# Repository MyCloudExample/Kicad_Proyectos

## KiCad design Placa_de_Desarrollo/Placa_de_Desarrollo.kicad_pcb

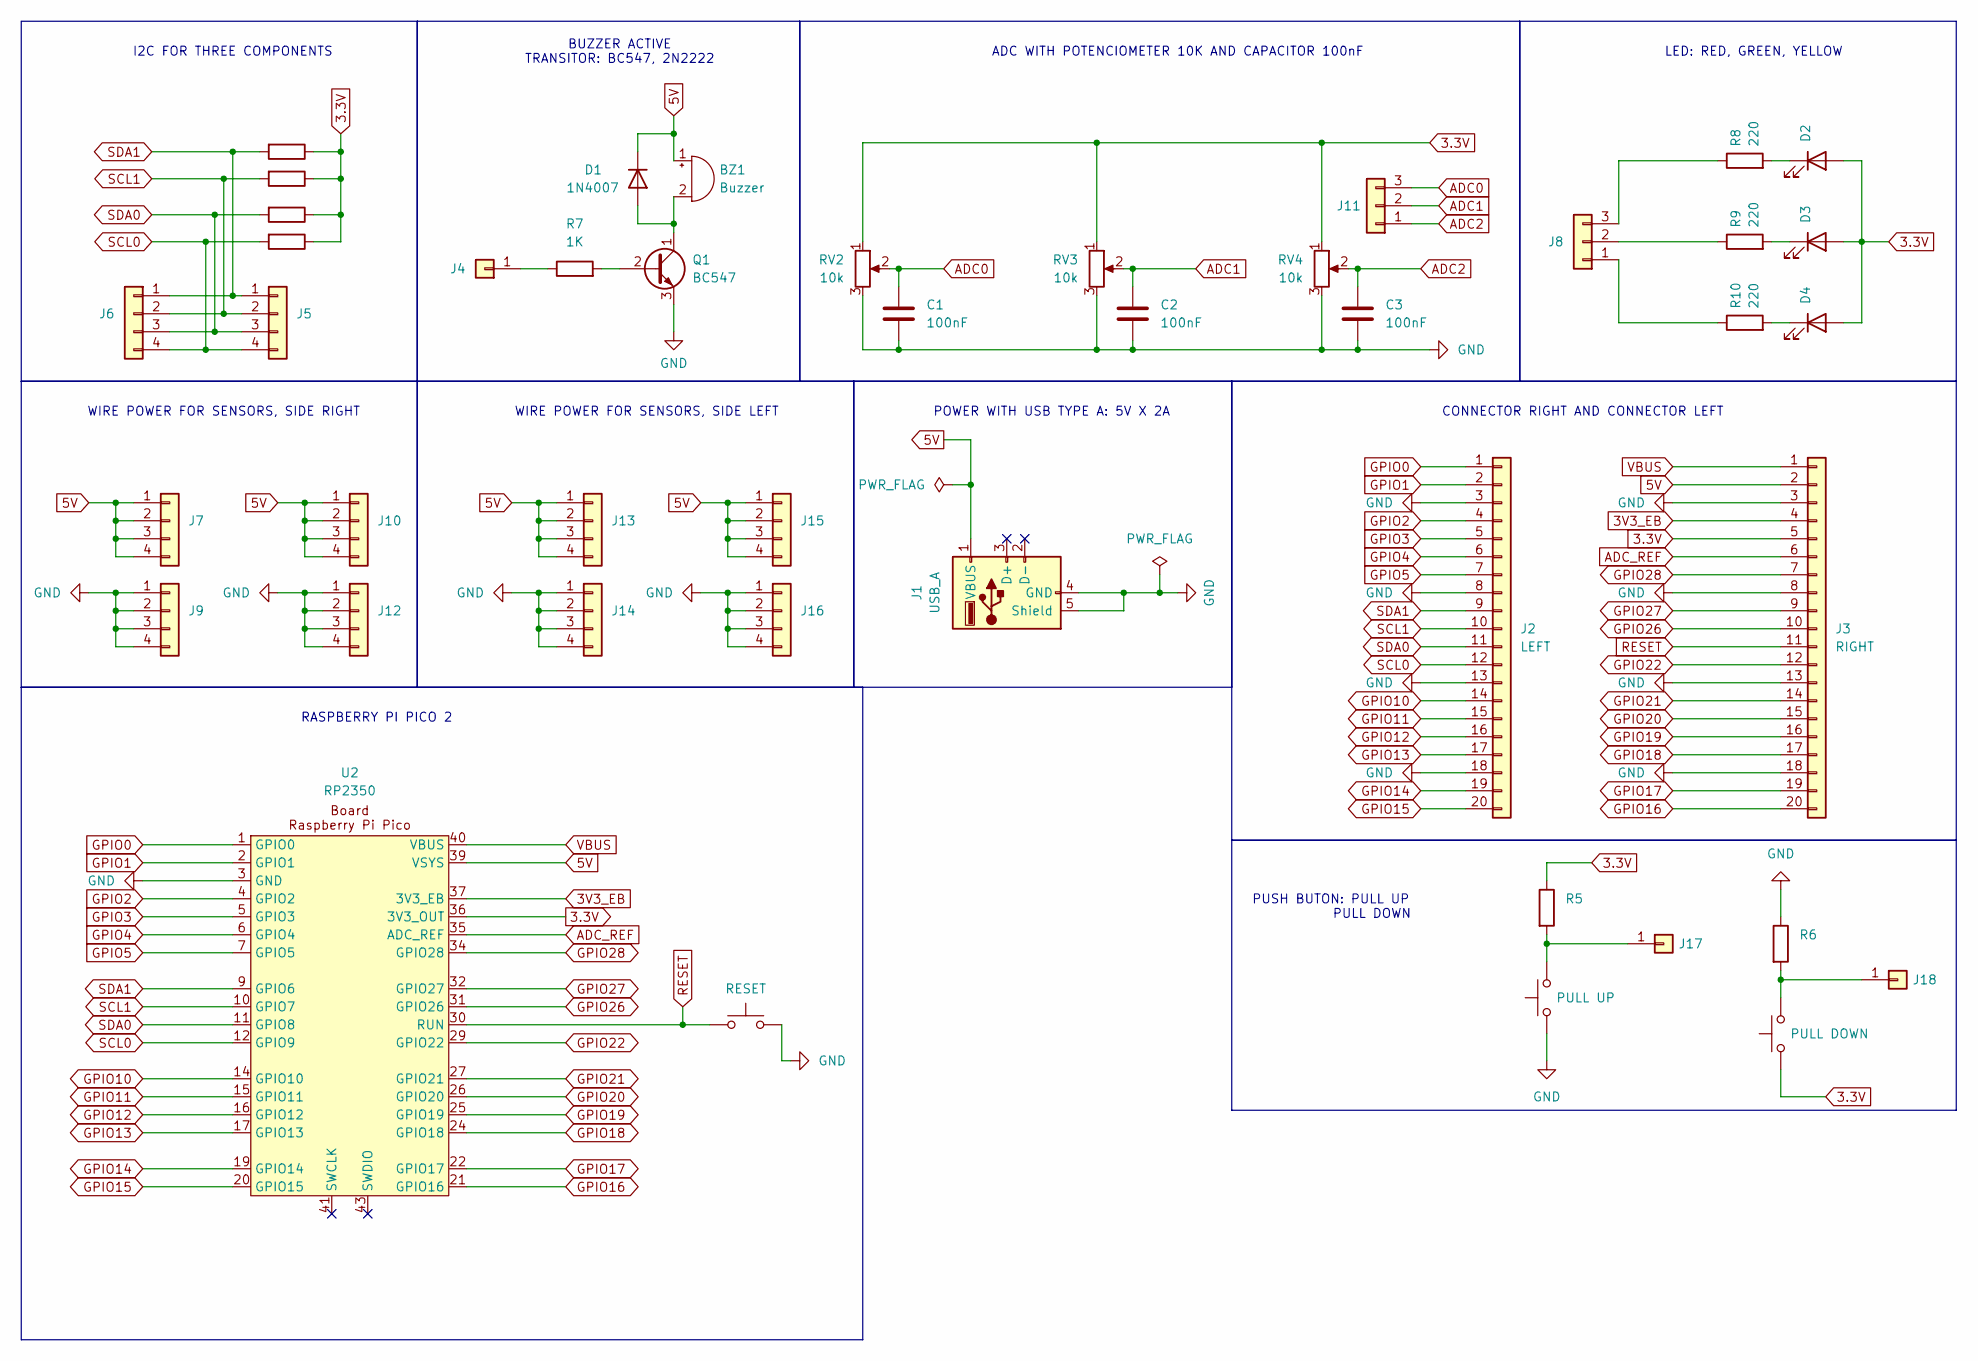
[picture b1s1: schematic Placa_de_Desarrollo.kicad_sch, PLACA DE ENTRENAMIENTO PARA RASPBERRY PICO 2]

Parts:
BZ1: Buzzer; Buzzer_12x9.5RM7.6
C1, C2, C3: 100nF; C_Disc_D8.0mm_W2.5mm_P5.00mm
D1: 1N4007; D_DO-41_SOD81_P10.16mm_Horizontal
D2, D3, D4: LED; LED_D5.0mm
J1: USB_A; USB_A_Molex_67643_Horizontal
J2: LEFT; PinHeader_1x20_P2.54mm_Vertical
J3: RIGHT; PinHeader_1x20_P2.54mm_Vertical
J4, J17, J18: Conn_01x01; PinHeader_1x01_P2.54mm_Vertical
J5, J6, J7, J9, J10, J12, J13, J14, J15, J16: Conn_01x04; PinHeader_1x04_P2.54mm_Vertical
J8, J11: Conn_01x03; PinHeader_1x03_P2.54mm_Vertical
Q1: BC547; TO-92_Inline
R1, R2, R3, R4: 4,7k; R_Axial_DIN0204_L3.6mm_D1.6mm_P7.62mm_Horizontal
R5, R6: 10K; R_Axial_DIN0204_L3.6mm_D1.6mm_P7.62mm_Horizontal
R7: 1K; R_Axial_DIN0204_L3.6mm_D1.6mm_P7.62mm_Horizontal
R8, R9, R10: 220; R_Axial_DIN0204_L3.6mm_D1.6mm_P7.62mm_Horizontal
RV2, RV3, RV4: 10k; Potentiometer_Piher_T-16H_Single_Horizontal
SW1: RESET; SW_PUSH_6mm
SW2: PULL DOWN; SW_PUSH_6mm
SW3: PULL UP; SW_PUSH_6mm
U2: RP2350; BoardF_Pi_Pico_RP2350

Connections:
3.3V: D2.2 (A), D3.2 (A), D4.2 (A), J3.5, R1.1, R2.1, R3.1, R4.1, R5.1, RV2.1, RV3.1, RV4.1, SW2.1, U2.36 (3V3_OUT)
3V3_EB: J3.4, U2.37 (3V3_EB)
5V: BZ1.1 (+), D1.1 (K), J1.1 (VBUS), J3.2, J7.1, J7.2, J7.3, J7.4, J10.1, J10.2, J10.3, J10.4, J13.1, J13.2, J13.3, J13.4, J15.1, J15.2, J15.3, J15.4, U2.39 (VSYS)
ADC0: C1.1, J11.3, RV2.2
ADC1: C2.1, J11.2, RV3.2
ADC2: C3.1, J11.1, RV4.2
ADC_REF: J3.6, U2.35 (ADC_REF)
GND: C1.2, C2.2, C3.2, J1.4 (GND), J1.5 (Shield), J2.3, J2.8, J2.13, J2.18, J3.3, J3.8, J3.13, J3.18, J9.1, J9.2, J9.3, J9.4, J12.1, J12.2, J12.3, J12.4, J14.1, J14.2, J14.3, J14.4, J16.1, J16.2, J16.3, J16.4, Q1.3 (E), R6.1, RV2.3, RV3.3, RV4.3, SW1.2, SW3.1, U2.3 (GND), U2.8 (GND), U2.13 (GND), U2.18 (GND), U2.23 (GND), U2.28 (GND), U2.33 (GND), U2.38 (GND), U2.42 (GND)
GPIO0: J2.1, U2.1 (GPIO0)
GPIO1: J2.2, U2.2 (GPIO1)
GPIO2: J2.4, U2.4 (GPIO2)
GPIO3: J2.5, U2.5 (GPIO3)
GPIO4: J2.6, U2.6 (GPIO4)
GPIO5: J2.7, U2.7 (GPIO5)
GPIO10: J2.14, U2.14 (GPIO10)
GPIO11: J2.15, U2.15 (GPIO11)
GPIO12: J2.16, U2.16 (GPIO12)
GPIO13: J2.17, U2.17 (GPIO13)
GPIO14: J2.19, U2.19 (GPIO14)
GPIO15: J2.20, U2.20 (GPIO15)
GPIO16: J3.20, U2.21 (GPIO16)
GPIO17: J3.19, U2.22 (GPIO17)
GPIO18: J3.17, U2.24 (GPIO18)
GPIO19: J3.16, U2.25 (GPIO19)
GPIO20: J3.15, U2.26 (GPIO20)
GPIO21: J3.14, U2.27 (GPIO21)
GPIO22: J3.12, U2.29 (GPIO22)
GPIO26: J3.10, U2.31 (GPIO26)
GPIO27: J3.9, U2.32 (GPIO27)
GPIO28: J3.7, U2.34 (GPIO28)
unnamed: BZ1.2 (-), D1.2 (A), Q1.1 (C)
unnamed: D2.1 (K), R8.2
unnamed: D3.1 (K), R9.2
unnamed: D4.1 (K), R10.2
unnamed: J4.1, R7.1
unnamed: J8.1, R10.1
unnamed: J8.2, R9.1
unnamed: J8.3, R8.1
unnamed: J17.1, R5.2, SW3.2
unnamed: J18.1, R6.2, SW2.2
unnamed: Q1.2 (B), R7.2
RESET: J3.11, SW1.1, U2.30 (RUN)
SCL0: J2.12, J5.4, J6.4, R4.2, U2.12 (GPIO9)
SCL1: J2.10, J5.2, J6.2, R2.2, U2.10 (GPIO7)
SDA0: J2.11, J5.3, J6.3, R3.2, U2.11 (GPIO8)
SDA1: J2.9, J5.1, J6.1, R1.2, U2.9 (GPIO6)
VBUS: J3.1, U2.40 (VBUS)

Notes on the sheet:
BUZZER ACTIVE TRANSITOR: BC547, 2N2222
WIRE POWER FOR SENSORS, SIDE RIGHT
ADC WITH POTENCIOMETER 10K AND CAPACITOR 100nF
POWER WITH USB TYPE A: 5V X 2A
PUSH BUTON: PULL UP PULL DOWN
LED: RED, GREEN, YELLOW
WIRE POWER FOR SENSORS, SIDE LEFT
CONNECTOR RIGHT AND CONNECTOR LEFT
I2C FOR THREE COMPONENTS
RASPBERRY PI PICO 2

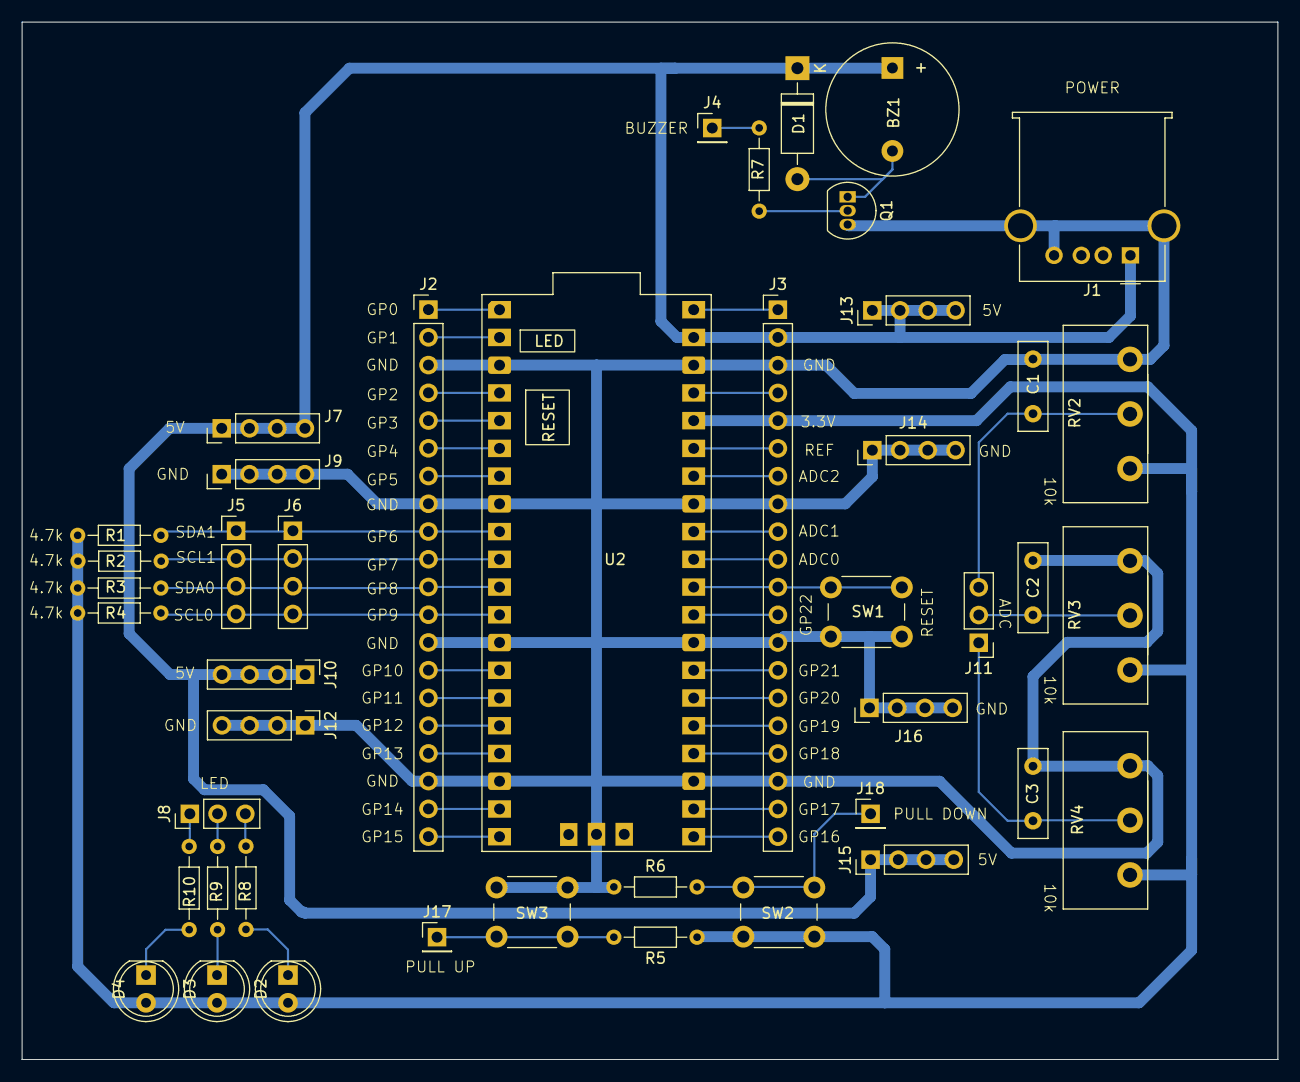
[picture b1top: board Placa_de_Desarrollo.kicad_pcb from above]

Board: 2 copper layers, 115.0 x 95.0 mm, 44 parts (0 on the bottom side), 47 nets.

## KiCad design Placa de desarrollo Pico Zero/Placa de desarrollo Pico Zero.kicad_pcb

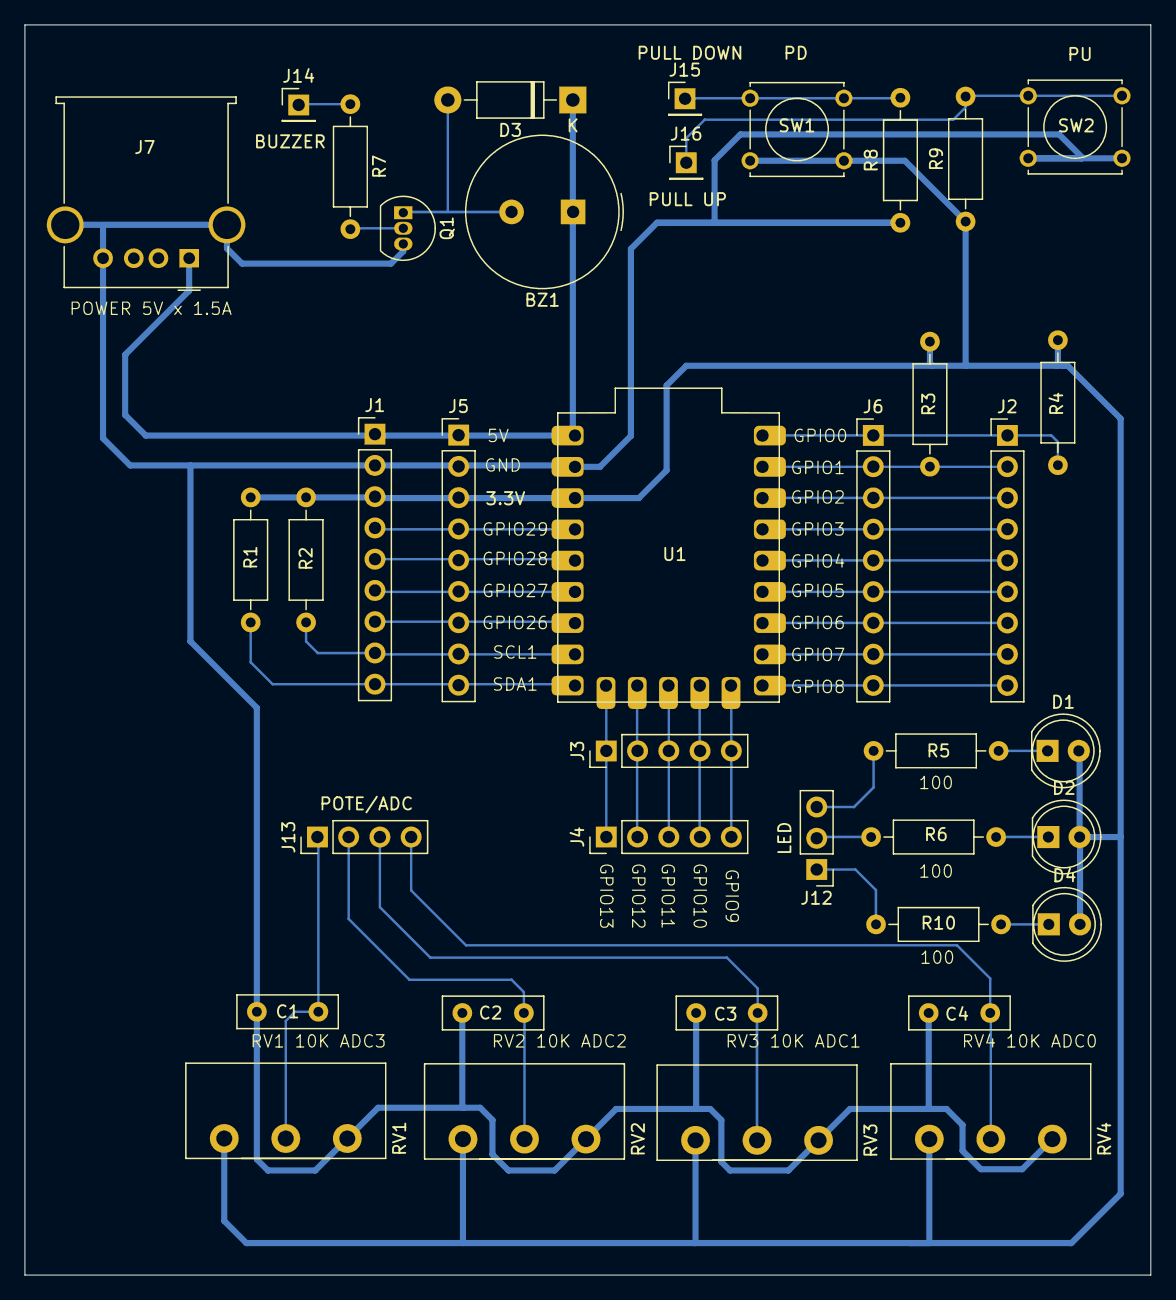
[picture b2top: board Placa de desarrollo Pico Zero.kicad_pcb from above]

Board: 2 copper layers, 91.5 x 101.6 mm, 39 parts (0 on the bottom side), 38 nets.

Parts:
BZ1: Buzzer; Buzzer_TDK_PS1240P02BT_D12.2mm_H6.5mm
C1, C2, C3, C4: 0.1uF; C_Disc_D8.0mm_W2.5mm_P5.00mm
D1, D2, D4: LED; LED_D5.0mm
D3: 1N4007; D_DO-41_SOD81_P10.16mm_Horizontal
J1: LEFT-MALE; PinHeader_1x09_P2.54mm_Vertical
J2: RIGHT-MALE; PinHeader_1x09_P2.54mm_Vertical
J3: DOWN-MALE; PinHeader_1x05_P2.54mm_Vertical
J4: DOWN-FEMALE; PinHeader_1x05_P2.54mm_Vertical
J5: LEFT-FEMALE; PinHeader_1x09_P2.54mm_Vertical
J6: RIGHT-FEMALE; PinHeader_1x09_P2.54mm_Vertical
J7: USB_A; USB_A_Molex_67643_Horizontal
J12: Conn_01x03; PinHeader_1x03_P2.54mm_Vertical
J13: Conn_01x04; PinHeader_1x04_P2.54mm_Vertical
J14, J15, J16: Conn_01x01; PinHeader_1x01_P2.54mm_Vertical
Q1: BC547; TO-92_Inline
R1, R2, R3, R4: 4K7; R_Axial_DIN0207_L6.3mm_D2.5mm_P10.16mm_Horizontal
R5, R6, R10: 100; R_Axial_DIN0207_L6.3mm_D2.5mm_P10.16mm_Horizontal
R7: 1k; R_Axial_DIN0207_L6.3mm_D2.5mm_P10.16mm_Horizontal
R8, R9: 10k; R_Axial_DIN0207_L6.3mm_D2.5mm_P10.16mm_Horizontal
RV1, RV2, RV3, RV4: 10k; Potentiometer_Piher_T-16H_Single_Horizontal
SW1, SW2: SW_Push; SW_Tactile_Straight_KSL0Axx1LFTR
U1: RP2040; BoardF_Pi_Pico_Zero_RP2040

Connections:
3V3: D1.2 (A), D2.2 (A), D4.2 (A), J1.3, J5.3, R1.2, R2.2, R3.2, R4.2, R9.1, RV1.1, RV2.1, RV3.1, RV4.1, SW1.2, U1.37 (3V3)
5V: BZ1.1 (+), D3.1 (K), J1.1, J5.1, J7.1 (VBUS), U1.39 (5V)
ADC0: C1.1, J13.1, RV1.2
ADC1: C2.1, J13.2, RV2.2
ADC3: C3.1, J13.3, RV3.2
ADC4: C4.1, J13.4, RV4.2
GND: C1.2, C2.2, C3.2, C4.2, J1.2, J5.2, J7.4 (GND), J7.5 (Shield), Q1.3 (E), R8.1, RV1.3, RV2.3, RV3.3, RV4.3, SW2.2, U1.38 (GND)
GPIO0: J2.1, J6.1, R4.1, U1.1 (GPIO0)
GPIO1: J2.2, J6.2, R3.1, U1.2 (GPIO1)
GPIO2: J2.3, J6.3, U1.4 (GPIO2)
GPIO3: J2.4, J6.4, U1.5 (GPIO3)
GPIO4: J2.5, J6.5, U1.6 (GPIO4)
GPIO5: J2.6, J6.6, U1.7 (GPIO5)
GPIO6: J2.7, J6.7, U1.9 (GPIO6)
GPIO7: J2.8, J6.8, U1.10 (GPIO7)
GPIO8: J2.9, J6.9, U1.11 (GPIO8)
GPIO9: J3.5, J4.5, U1.12 (GPIO9)
GPIO10: J3.4, J4.4, U1.14 (GPIO10)
GPIO11: J3.3, J4.3, U1.15 (GPIO11)
GPIO26/ADC0: J1.7, J5.7, U1.31 (GPIO26)
GPIO27/ADC1: J1.6, J5.6, U1.32 (GPIO27)
GPIO28/ADC2: J1.5, J5.5, U1.34 (GPIO28)
GPIO29/ADC3: J1.4, J5.4, U1.35 (GPIO29)
unnamed: BZ1.2 (-), D3.2 (A), Q1.1 (C)
unnamed: D1.1 (K), R5.2
unnamed: D2.1 (K), R6.2
unnamed: D4.1 (K), R10.2
unnamed: J12.1, R10.1
unnamed: J12.2, R6.1
unnamed: J12.3, R5.1
unnamed: J14.1, R7.1
unnamed: J15.1, R8.2, SW1.1
unnamed: J16.1, R9.2, SW2.1
unnamed: Q1.2 (B), R7.2
SCL0: J3.1, J4.1, U1.17 (GPIO17)
SCL1: J1.8, J5.8, R2.1, U1.20 (GPIO15)
SDA0: J3.2, J4.2, U1.16 (GPIO12)
SDA1: J1.9, J5.9, R1.1, U1.19 (GPIO14)

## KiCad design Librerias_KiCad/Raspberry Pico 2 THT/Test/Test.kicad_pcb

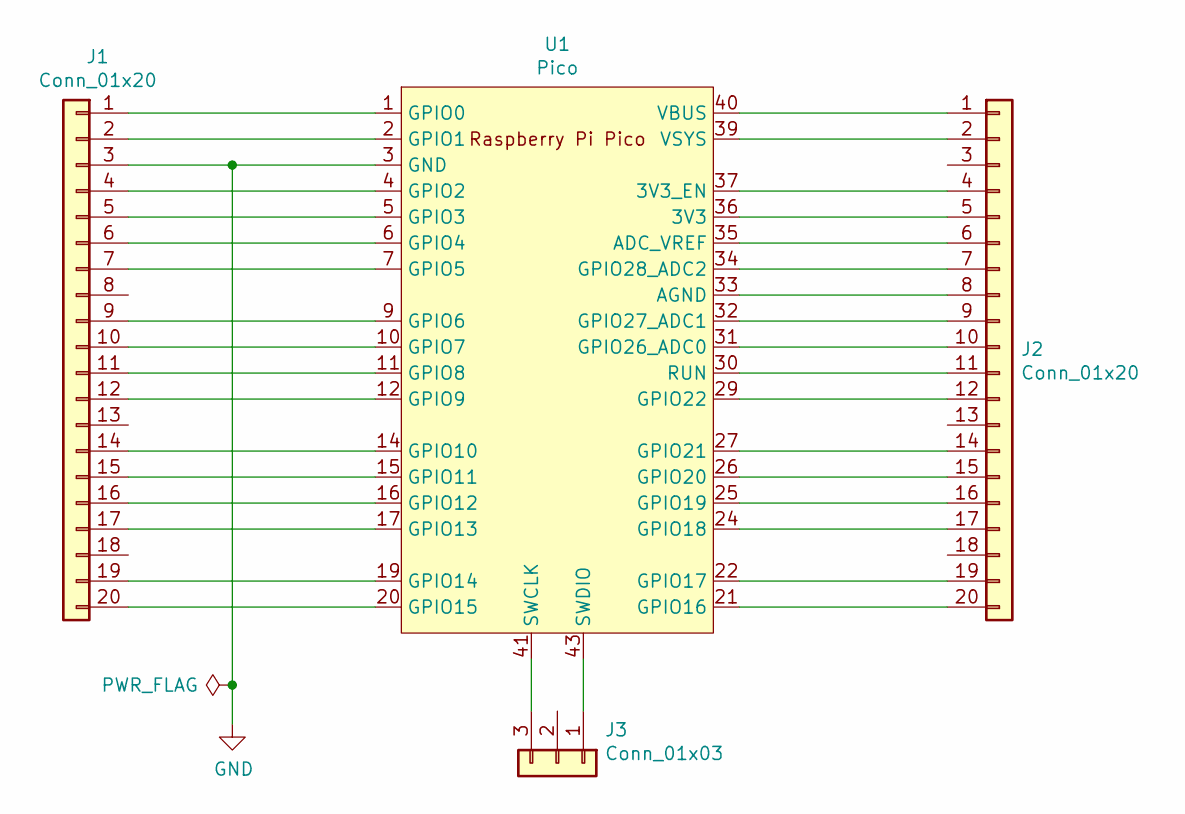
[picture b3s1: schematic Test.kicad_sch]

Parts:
J1, J2: Conn_01x20; PinSocket_1x20_P1.00mm_Vertical
J3: Conn_01x03; PinSocket_1x03_P1.00mm_Vertical
U1: Pico; RPi_Pico_SMD_TH

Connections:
GND: J1.3, J1.8, J1.13, J1.18, J2.3, J2.13, J2.18, J3.2, U1.3 (GND), U1.8 (GND), U1.13 (GND), U1.18 (GND), U1.23 (GND), U1.28 (GND), U1.38 (GND), U1.42 (GND)
unnamed: J1.1, U1.1 (GPIO0)
unnamed: J1.2, U1.2 (GPIO1)
unnamed: J1.4, U1.4 (GPIO2)
unnamed: J1.5, U1.5 (GPIO3)
unnamed: J1.6, U1.6 (GPIO4)
unnamed: J1.7, U1.7 (GPIO5)
unnamed: J1.9, U1.9 (GPIO6)
unnamed: J1.10, U1.10 (GPIO7)
unnamed: J1.11, U1.11 (GPIO8)
unnamed: J1.12, U1.12 (GPIO9)
unnamed: J1.14, U1.14 (GPIO10)
unnamed: J1.15, U1.15 (GPIO11)
unnamed: J1.16, U1.16 (GPIO12)
unnamed: J1.17, U1.17 (GPIO13)
unnamed: J1.19, U1.19 (GPIO14)
unnamed: J1.20, U1.20 (GPIO15)
unnamed: J2.1, U1.40 (VBUS)
unnamed: J2.2, U1.39 (VSYS)
unnamed: J2.4, U1.37 (3V3_EN)
unnamed: J2.5, U1.36 (3V3)
unnamed: J2.6, U1.35 (ADC_VREF)
unnamed: J2.7, U1.34 (GPIO28_ADC2)
unnamed: J2.8, U1.33 (AGND)
unnamed: J2.9, U1.32 (GPIO27_ADC1)
unnamed: J2.10, U1.31 (GPIO26_ADC0)
unnamed: J2.11, U1.30 (RUN)
unnamed: J2.12, U1.29 (GPIO22)
unnamed: J2.14, U1.27 (GPIO21)
unnamed: J2.15, U1.26 (GPIO20)
unnamed: J2.16, U1.25 (GPIO19)
unnamed: J2.17, U1.24 (GPIO18)
unnamed: J2.19, U1.22 (GPIO17)
unnamed: J2.20, U1.21 (GPIO16)
unnamed: J3.1, U1.43 (SWDIO)
unnamed: J3.3, U1.41 (SWCLK)

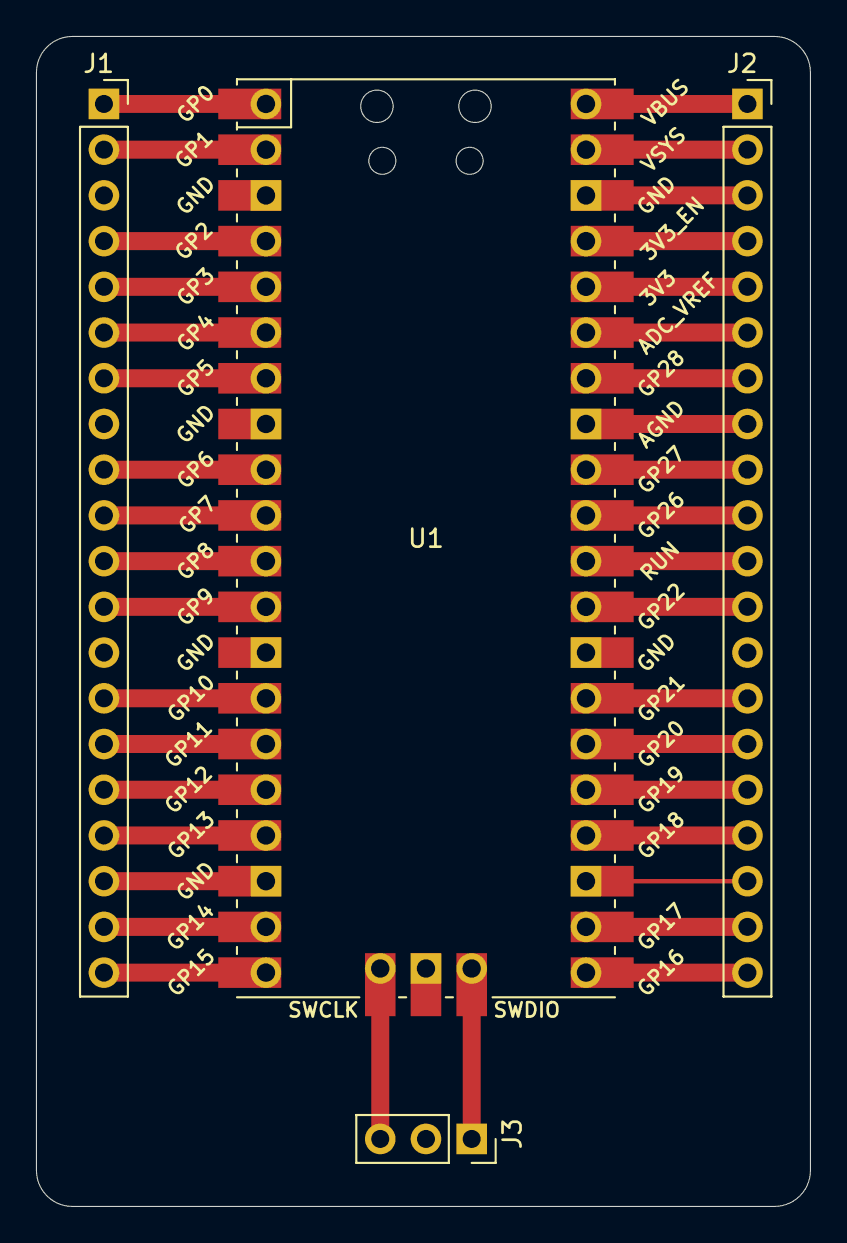
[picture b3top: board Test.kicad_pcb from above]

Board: 2 copper layers, 43.0 x 65.0 mm, 4 parts (0 on the bottom side), 36 nets.

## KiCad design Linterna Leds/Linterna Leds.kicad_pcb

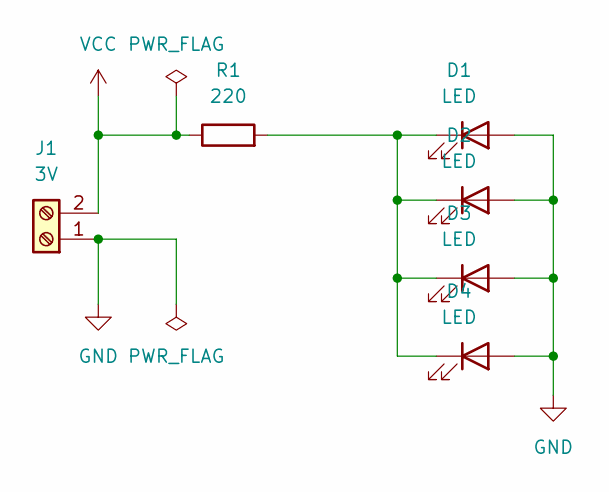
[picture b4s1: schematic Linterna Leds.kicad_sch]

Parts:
D1, D2, D3, D4: LED; LED_D5.0mm
J1: 3V; TerminalBlock_Xinya_XY308-2.54-2P_1x02_P2.54mm_Horizontal
R1: 220; R_Axial_DIN0207_L6.3mm_D2.5mm_P10.16mm_Horizontal

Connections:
GND: D1.2 (A), D2.2 (A), D3.2 (A), D4.2 (A), J1.1
unnamed: D1.1 (K), D2.1 (K), D3.1 (K), D4.1 (K), R1.2
VCC: J1.2, R1.1

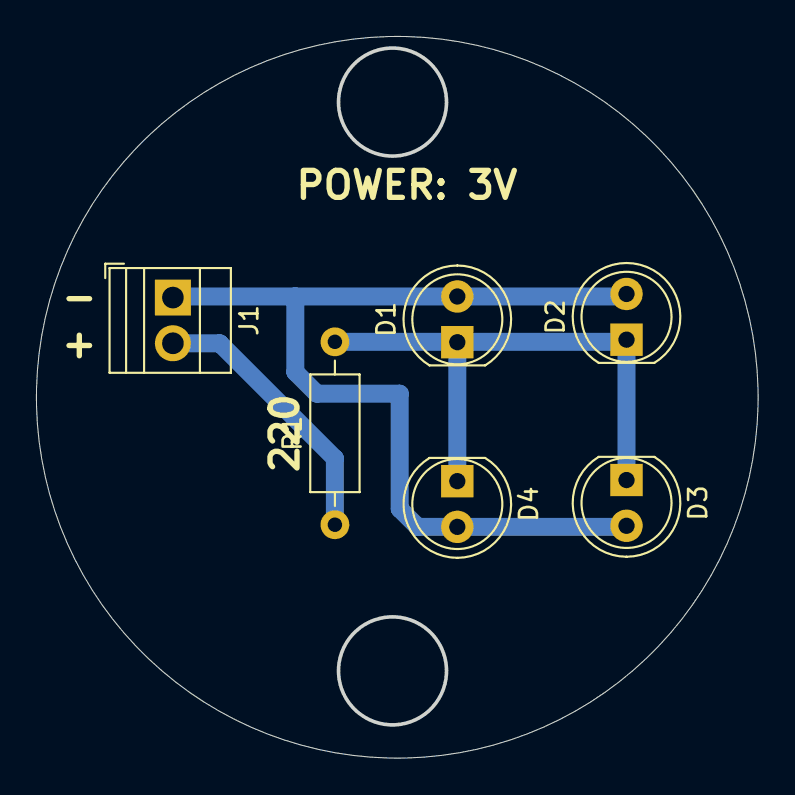
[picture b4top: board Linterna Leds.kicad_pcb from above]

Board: 2 copper layers, 40.1 x 40.1 mm, 6 parts (0 on the bottom side), 3 nets.

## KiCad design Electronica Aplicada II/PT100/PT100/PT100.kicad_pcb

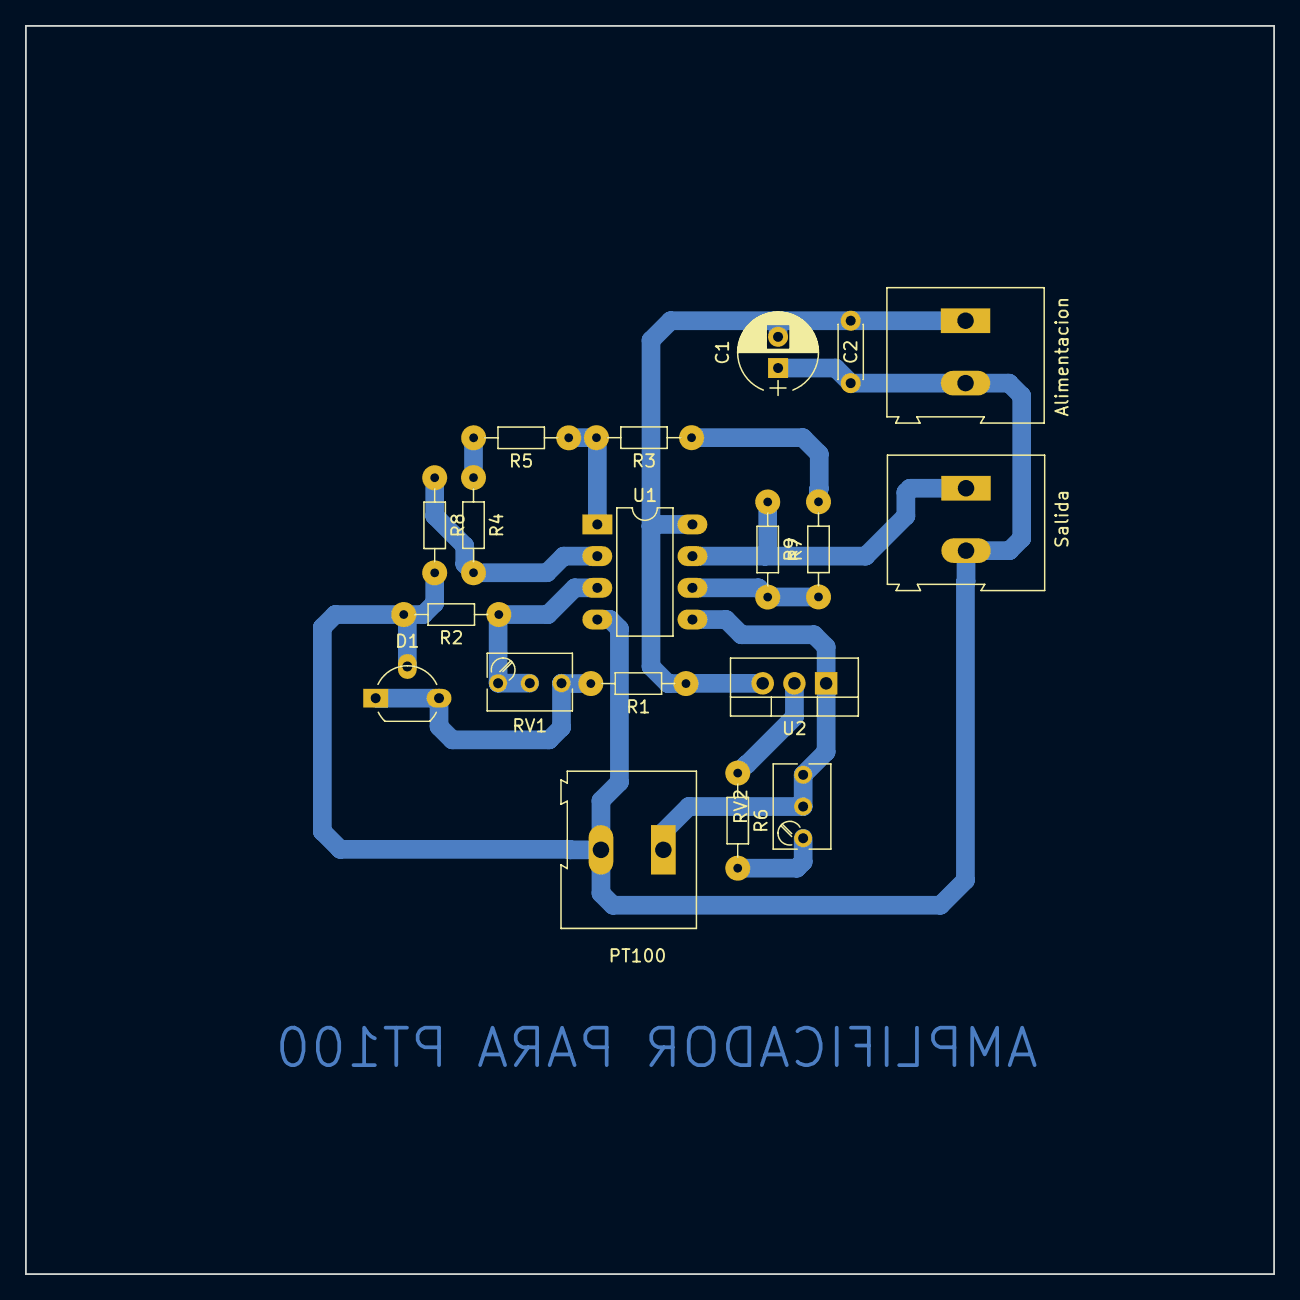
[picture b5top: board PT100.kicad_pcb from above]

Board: 2 copper layers, 100.0 x 100.0 mm, 19 parts (0 on the bottom side), 13 nets.

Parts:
Alimentacion: TerminalBlock_Altech_AK300-2_P5.00mm
C1: 100uF; CP_Radial_D6.3mm_P2.50mm
C2: 0,1uF; C_Disc_D4.3mm_W1.9mm_P5.00mm
D1: TL431LP; TO-92_Molded_Wide_Oval
PT100: TerminalBlock_Altech_AK300-2_P5.00mm
R1: 4k7; R_Axial_DIN0204_L3.6mm_D1.6mm_P7.62mm_Horizontal
R2: 470; R_Axial_DIN0204_L3.6mm_D1.6mm_P7.62mm_Horizontal
R3, R4, R5, R7: 1k2; R_Axial_DIN0204_L3.6mm_D1.6mm_P7.62mm_Horizontal
R6: 180; R_Axial_DIN0204_L3.6mm_D1.6mm_P7.62mm_Horizontal
R8, R9: 10k; R_Axial_DIN0204_L3.6mm_D1.6mm_P7.62mm_Horizontal
RV1: 1k5; Potentiometer_Trimmer_Bourns_3266Y
RV2: 100; Potentiometer_Trimmer_Bourns_3266Y
Salida: TerminalBlock_Altech_AK300-2_P5.00mm
U1: LM358; DIP-8_W7.62mm_LongPads
U2: LM317_3PinPackage; TO-220-3_Vertical

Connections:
GNDREF: Alimentacion.2, C1.1, C2.1, D1.2, PT100.2, R2.2, R8.2, Salida.2, U1.4
unnamed: D1.1, D1.3, R1.2, RV1.3
unnamed: PT100.1, RV2.2, RV2.3, U1.5, U2.1
unnamed: R2.1, RV1.1, RV1.2, U1.3
unnamed: R3.1, R7.2
unnamed: R3.2, R5.1, U1.1
unnamed: R4.1, R5.2
unnamed: R4.2, R8.1, U1.2
unnamed: R6.1, U2.2
unnamed: R6.2, RV2.1
unnamed: R7.1, R9.2, U1.6
unnamed: R9.1, Salida.1, U1.7
VDD: Alimentacion.1, C1.2, C2.2, R1.1, U1.8, U2.3

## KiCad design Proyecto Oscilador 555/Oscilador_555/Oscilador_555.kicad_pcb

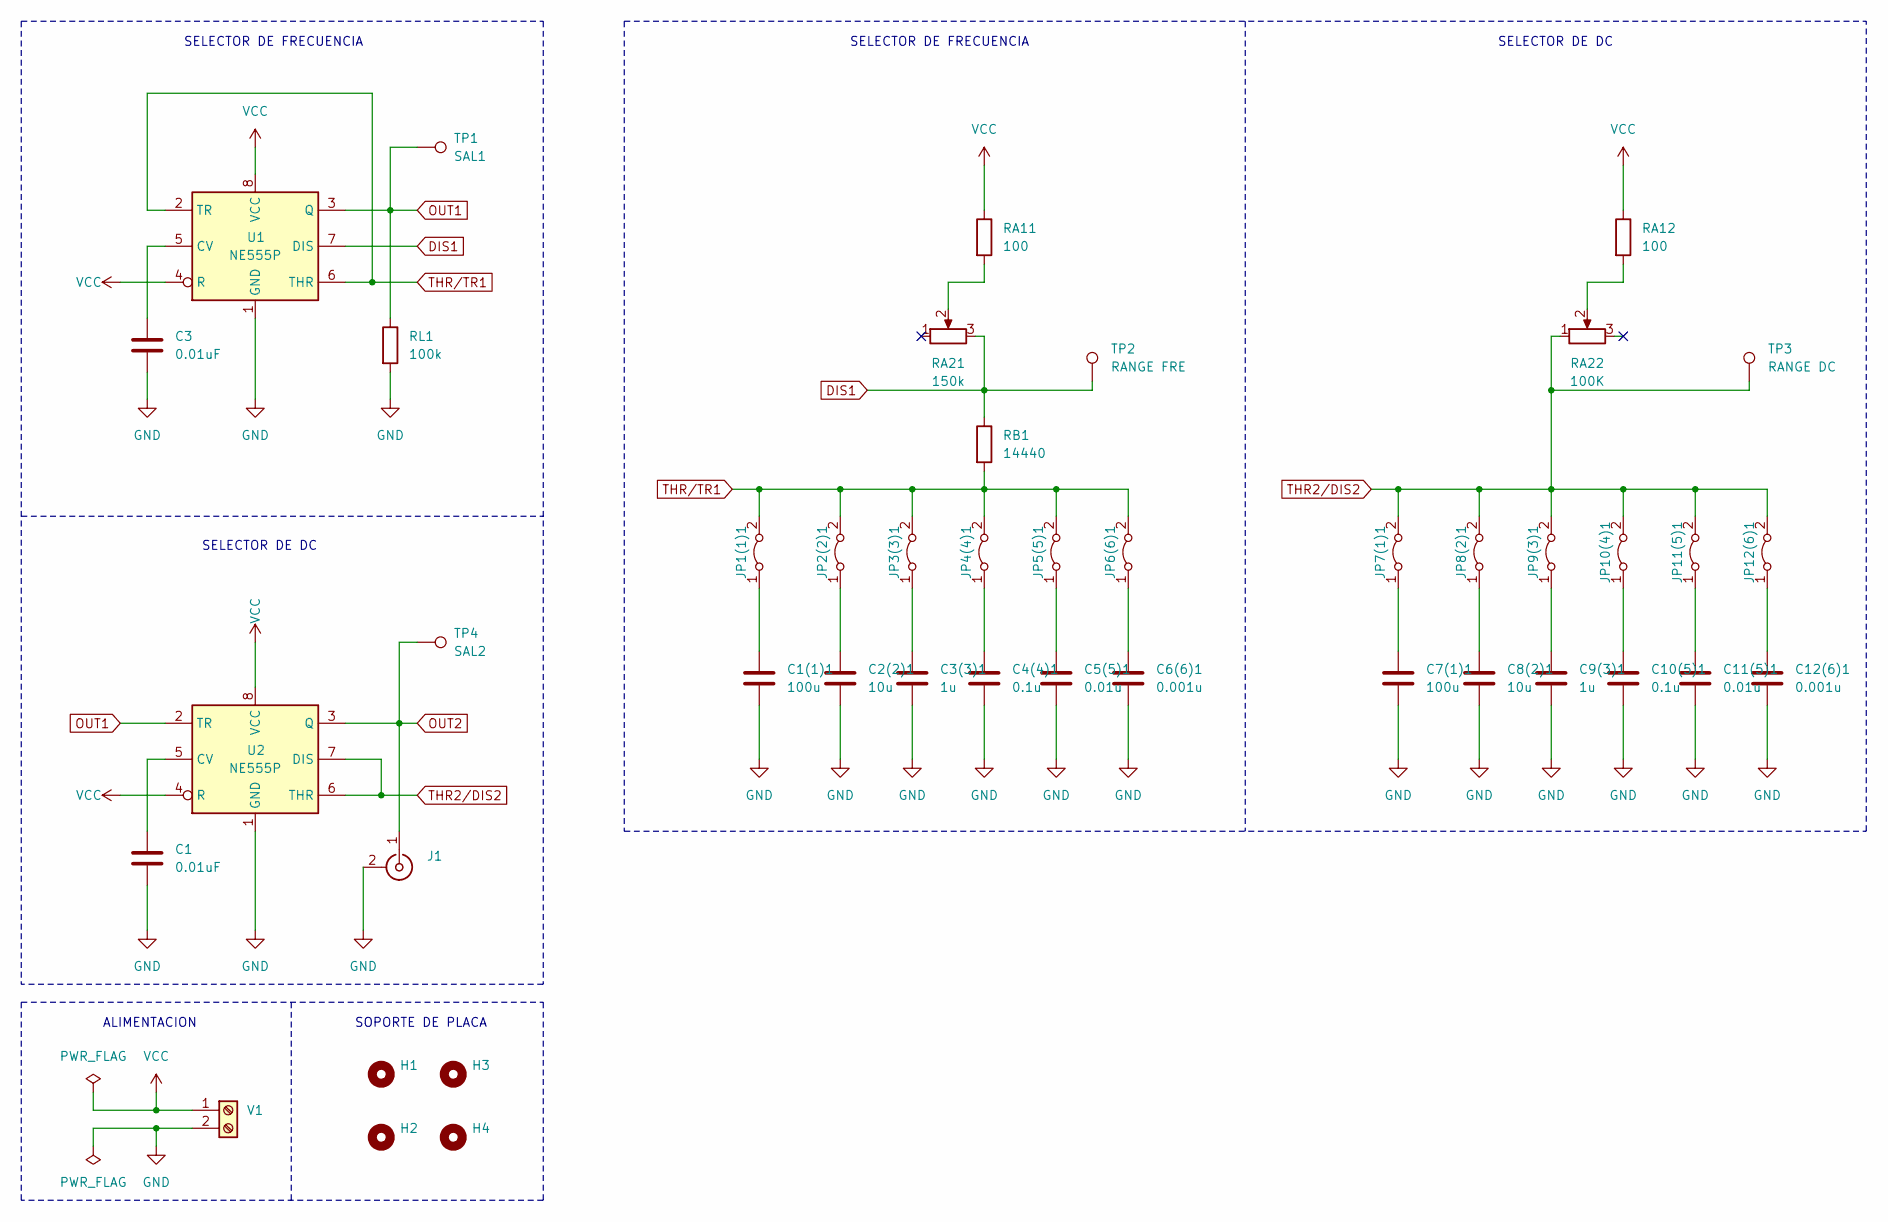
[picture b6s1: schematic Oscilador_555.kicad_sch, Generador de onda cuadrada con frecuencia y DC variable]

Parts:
C1, C3: 0.01uF; C_Disc_D7.0mm_W2.5mm_P5.00mm
C1(1)1, C7(1)1: 100u; C_Radial_D12.5mm_H20.0mm_P5.00mm
C2(2)1, C8(2)1: 10u; C_Radial_D8.0mm_H7.0mm_P3.50mm
C3(3)1, C9(3)1: 1u; C_Rect_L16.5mm_W7.0mm_P15.00mm_MKT
C4(4)1, C10(5)1: 0.1u; C_Disc_D7.0mm_W2.5mm_P5.00mm
C5(5)1, C11(5)1: 0.01u; C_Disc_D7.0mm_W2.5mm_P5.00mm
C6(6)1, C12(6)1: 0.001u; C_Disc_D7.0mm_W2.5mm_P5.00mm
H1, H2, H3, H4: MountingHole; MountingHole_5mm
J1: Conn_Coaxial; BNC_TEConnectivity_1478204_Vertical
JP1(1)1, JP2(2)1, JP3(3)1, JP4(4)1, JP5(5)1, JP6(6)1, JP7(1)1, JP8(2)1, JP9(3)1, JP10(4)1, JP11(5)1, JP12(6)1: Jumper_2_Bridged; TestPoint_2Pads_Pitch2.54mm_Drill0.8mm
RA11, RA12: 100; R_Axial_DIN0204_L3.6mm_D1.6mm_P5.08mm_Horizontal
RA21: 150k; Potentiometer_Omeg_PC16BU_Horizontal
RA22: 100K; Potentiometer_Omeg_PC16BU_Horizontal
RB1: 14440; R_Axial_DIN0204_L3.6mm_D1.6mm_P5.08mm_Horizontal
RL1: 100k; R_Axial_DIN0204_L3.6mm_D1.6mm_P5.08mm_Horizontal
TP1: SAL1; Pin_D1.3mm_L10.0mm_W3.5mm_Flat
TP2: RANGE FRE; Pin_D1.3mm_L10.0mm_W3.5mm_Flat
TP3: RANGE DC; Pin_D1.3mm_L10.0mm_W3.5mm_Flat
TP4: SAL2; Pin_D1.3mm_L10.0mm_W3.5mm_Flat
U1, U2: NE555P; DIP-8_W7.62mm
V1: 12V; TerminalBlock_bornier-2_P5.08mm

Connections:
DIS1: RA21.3, RB1.1, TP2.1, U1.7 (DIS)
GND: C1.2, C1(1)1.2, C2(2)1.2, C3.2, C3(3)1.2, C4(4)1.2, C5(5)1.2, C6(6)1.2, C7(1)1.2, C8(2)1.2, C9(3)1.2, C10(5)1.2, C11(5)1.2, C12(6)1.2, J1.2 (Ext), RL1.2, U1.1 (GND), U2.1 (GND), V1.2
unnamed: C1(1)1.1, JP1(1)1.1 (A)
unnamed: C1.1, U2.5 (CV)
unnamed: C2(2)1.1, JP2(2)1.1 (A)
unnamed: C3(3)1.1, JP3(3)1.1 (A)
unnamed: C3.1, U1.5 (CV)
unnamed: C4(4)1.1, JP4(4)1.1 (A)
unnamed: C5(5)1.1, JP5(5)1.1 (A)
unnamed: C6(6)1.1, JP6(6)1.1 (A)
unnamed: C7(1)1.1, JP7(1)1.1 (A)
unnamed: C8(2)1.1, JP8(2)1.1 (A)
unnamed: C9(3)1.1, JP9(3)1.1 (A)
unnamed: C10(5)1.1, JP10(4)1.1 (A)
unnamed: C11(5)1.1, JP11(5)1.1 (A)
unnamed: C12(6)1.1, JP12(6)1.1 (A)
unnamed: RA11.2, RA21.2
unnamed: RA12.2, RA22.2
OUT1: RL1.1, TP1.1, U1.3 (Q), U2.2 (TR)
OUT2: J1.1 (In), TP4.1, U2.3 (Q)
THR2/DIS2: JP7(1)1.2 (B), JP8(2)1.2 (B), JP9(3)1.2 (B), JP10(4)1.2 (B), JP11(5)1.2 (B), JP12(6)1.2 (B), RA22.1, TP3.1, U2.6 (THR), U2.7 (DIS)
THR/TR1: JP1(1)1.2 (B), JP2(2)1.2 (B), JP3(3)1.2 (B), JP4(4)1.2 (B), JP5(5)1.2 (B), JP6(6)1.2 (B), RB1.2, U1.2 (TR), U1.6 (THR)
VCC: RA11.1, RA12.1, U1.4 (R), U1.8 (VCC), U2.4 (R), U2.8 (VCC), V1.1

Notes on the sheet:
SOPORTE DE PLACA
SELECTOR DE DC
SELECTOR DE FRECUENCIA
ALIMENTACION

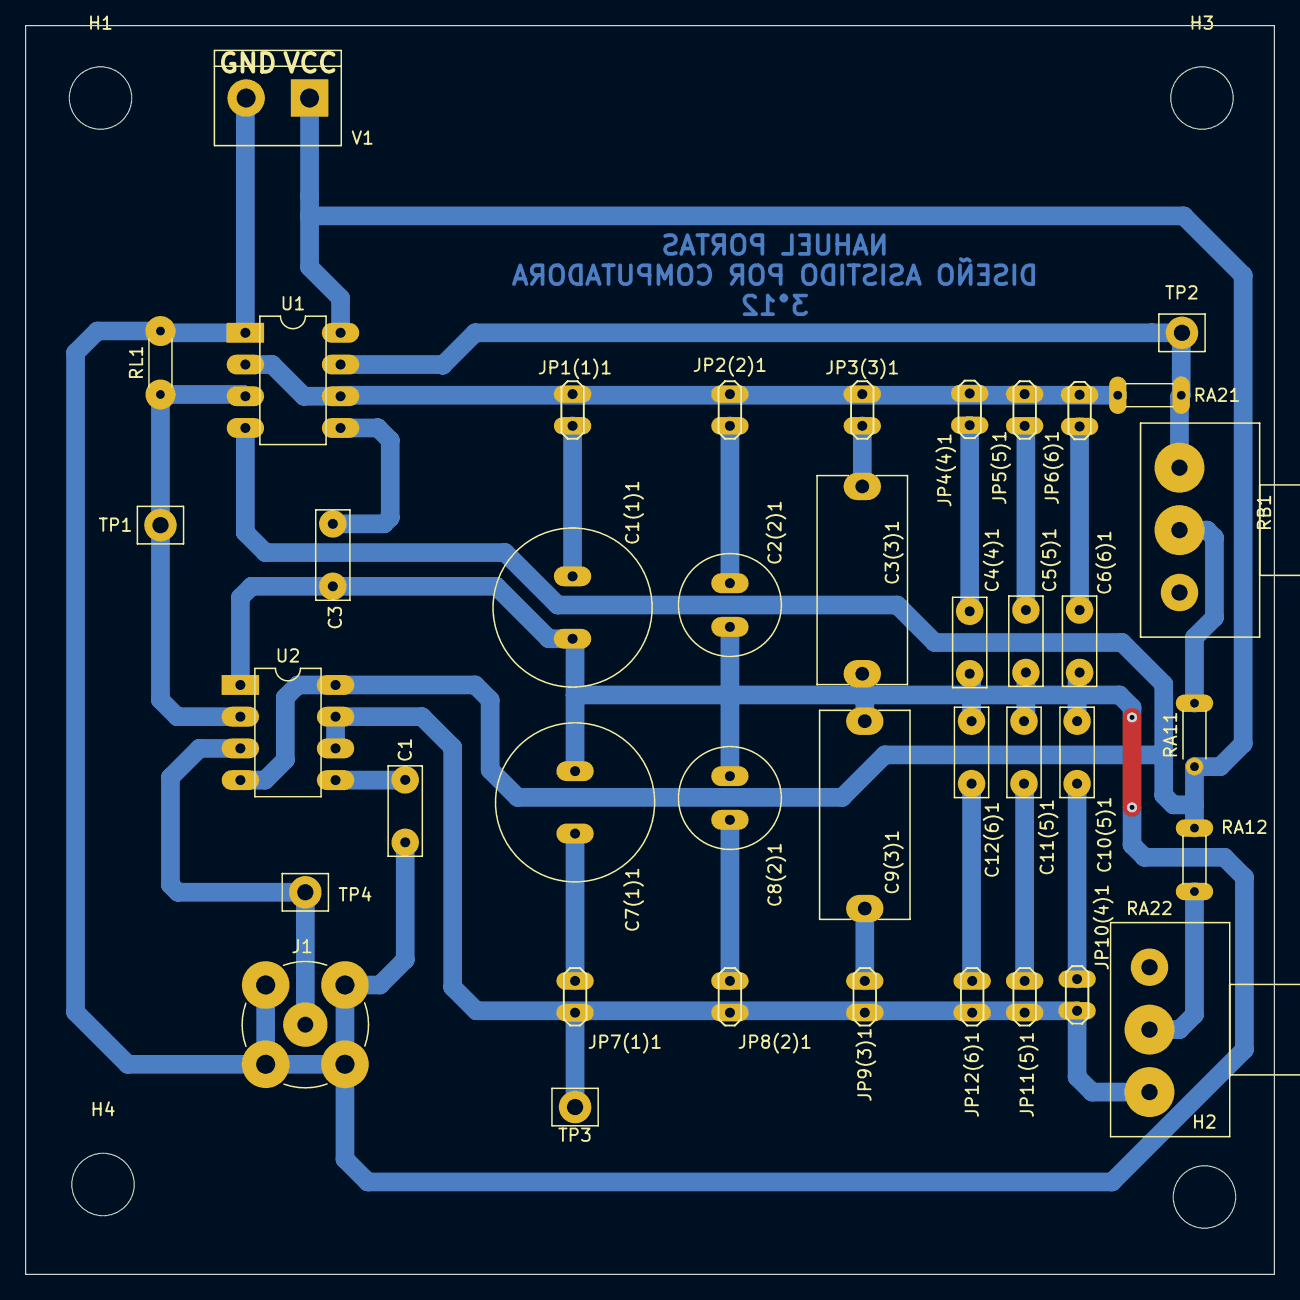
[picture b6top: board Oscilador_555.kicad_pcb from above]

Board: 2 copper layers, 100.0 x 100.0 mm, 44 parts (0 on the bottom side), 23 nets.

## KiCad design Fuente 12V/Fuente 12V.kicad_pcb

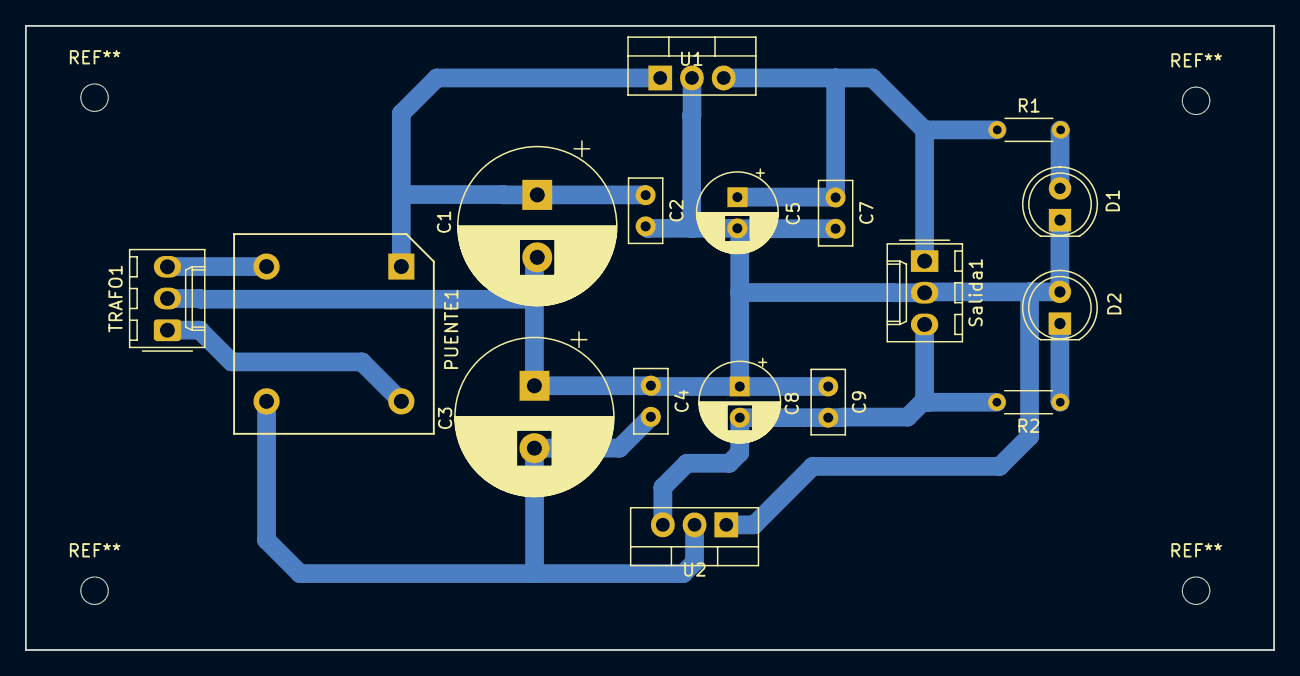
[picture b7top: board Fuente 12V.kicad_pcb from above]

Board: 2 copper layers, 100.0 x 50.0 mm, 17 parts (0 on the bottom side), 9 nets.

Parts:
C1, C3: 1000uF; CP_Radial_D12.5mm_P5.00mm
C2, C4, C7, C9: 0,1uF; C_Disc_D5.0mm_W2.5mm_P2.50mm
C5, C8: 10uF; CP_Radial_D6.3mm_P2.50mm
D1, D2: LED_D5.0mm
PUENTE1: Diode_Bridge_15.7x15.7
R1, R2: 1K-2K2; R_Axial_DIN0204_L3.6mm_D1.6mm_P5.08mm_Horizontal
Salida1: -12V GND +12V; Molex_KK-254_AE-6410-03A_1x03_P2.54mm_Vertical
TRAFO1: -12V GND +12V; Molex_KK-254_AE-6410-03A_1x03_P2.54mm_Vertical
U1: LM7812_TO220; TO-220-3_Vertical
U2: LM7912_TO220; TO-220-3_Vertical

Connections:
Earth: C1.2, C2.2, C3.1, C4.1, C5.2, C7.2, C8.1, C9.1, D1.1, D2.2, Salida1.2, TRAFO1.2, U1.2, U2.1
unnamed: C1.1, C2.1, PUENTE1.3, U1.1
unnamed: C3.2, C4.2, PUENTE1.1, U2.2
unnamed: C5.1, C7.1, R1.1, Salida1.1, U1.3
unnamed: C8.2, C9.2, R2.2, Salida1.3, U2.3
unnamed: D1.2, R1.2
unnamed: D2.1, R2.1
unnamed: PUENTE1.2, TRAFO1.1
unnamed: PUENTE1.4, TRAFO1.3
